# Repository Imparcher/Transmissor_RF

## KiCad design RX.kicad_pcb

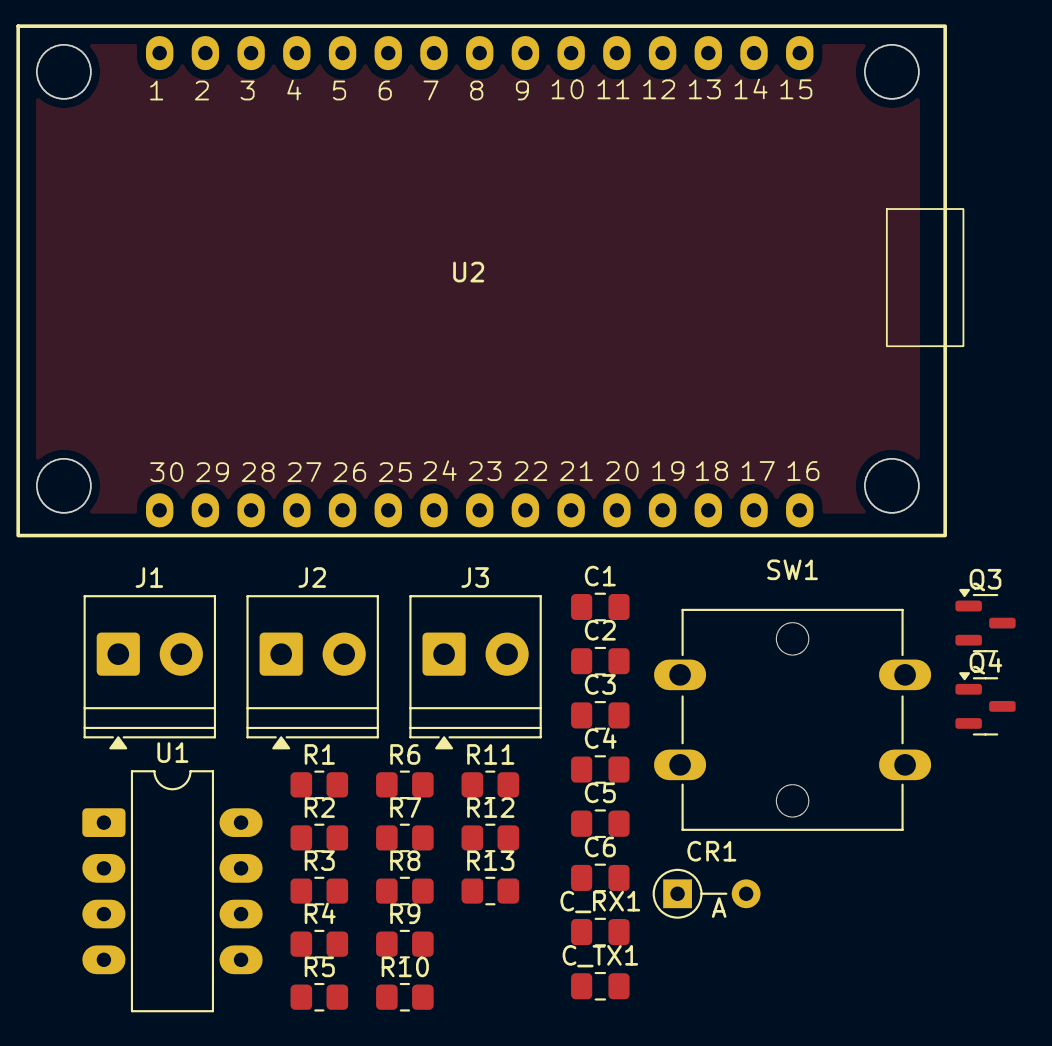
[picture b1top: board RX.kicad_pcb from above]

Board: 2 copper layers, 30 parts (0 on the bottom side), 16 nets, no tracks yet.

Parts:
C1, C2, C4, C5, C6: 1uF; C_0805_2012Metric_Pad1.18x1.45mm_HandSolder
C3: 25pF; C_0805_2012Metric_Pad1.18x1.45mm_HandSolder
CR1: 1N4148; D_DO-35_SOD27_P3.81mm_Vertical_AnodeUp
C_RX1: 1uF; C_0805_2012Metric_Pad1.18x1.45mm_HandSolder
C_TX1: 1uF; C_0805_2012Metric_Pad1.18x1.45mm_HandSolder
J1, J2: Screw_Terminal_01x01; TerminalBlock_Phoenix_PT-1,5-2-3.5-H_1x02_P3.50mm_Horizontal
J3: Screw_Terminal_01x02; TerminalBlock_Phoenix_PT-1,5-2-3.5-H_1x02_P3.50mm_Horizontal
Q3, Q4: BC847; SOT-23
R1, R7: 180k; R_0805_2012Metric_Pad1.20x1.40mm_HandSolder
R2, R8: 120k; R_0805_2012Metric_Pad1.20x1.40mm_HandSolder
R3, R4, R9, R10: 3.3k; R_0805_2012Metric_Pad1.20x1.40mm_HandSolder
R5: 250k; R_0805_2012Metric_Pad1.20x1.40mm_HandSolder
R6: 1k; R_0805_2012Metric_Pad1.20x1.40mm_HandSolder
R11: 10k-30k; R_0805_2012Metric_Pad1.20x1.40mm_HandSolder
R12: 15k; R_0805_2012Metric_Pad1.20x1.40mm_HandSolder
R13: 10k-20k; R_0805_2012Metric_Pad1.20x1.40mm_HandSolder
SW1: SW_SPST; SW_SPST_Omron_B3F-40xx
U1: LM358; CERDIP-8_W7.62mm_SideBrazed_LongPads
U2: ESP32_30pin

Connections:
+5V: C4.2, R1.1, R3.1, R7.1, R9.1, R12.2, SW1.2 (B), U1.8 (V+), U2.1 (VIN)
/AmpOp: R11.2, U1.1, U1.5 (+)
/Antena_RX: C_RX1.2, J2.1
/Antena_TX: C_TX1.1, J1.1
/Bateria: J3.2, SW1.1 (A)
/Current_Amp: C5.2, Q3.2 (E), R4.1
/Retificadora: C3.1, CR1.1, R5.1, U1.2 (-)
/Voltage_Amp: C2.1, Q4.3 (C), R9.2
GND: C3.2, C6.1, C_RX1.1, C_TX1.2, J3.1, R2.2, R4.2, R5.2, R6.1, R8.2, R10.2, R13.2, U1.4 (V-), U2.2 (GND)
unnamed: C2.2, CR1.2
unnamed: C1.2, Q3.1 (B), R1.2, R2.1
unnamed: C4.1, Q3.3 (C), R3.2
unnamed: C5.1, Q4.1 (B), R7.2, R8.1
unnamed: C6.2, Q4.2 (E), R10.1
unnamed: R6.2, R11.1, U1.3 (+)
unnamed: R12.1, R13.1, U1.6 (-)

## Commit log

2025-06-23 Create RX
